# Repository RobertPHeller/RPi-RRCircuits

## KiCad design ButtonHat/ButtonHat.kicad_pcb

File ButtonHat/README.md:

# ButtonHat

This is a RPi HAT board to interface up to 12 push buttons with hardware 
debouncing (using 74ahc14 Hex Schmitt-Trigger Inverters) to a RPi.  Jumpers 
are used to map the buttons to GPIO pins.  This was a simple "thought 
experiment" to see if this was possible.

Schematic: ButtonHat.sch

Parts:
C1, C2, C3, C4, C5, C6, C9, C10, C11, C12, C13, C14: 10 nf; Mouser Part Number 80-C317C103M5U
C7, C8: .1 uf; Mouser Part Number 21RZ310-RC
J0: RPI_GPIO; Mouser Part Number 855-M20-6102045
J1: Buttons 1 to 6; Mouser Part Number 538-90147-1106
J2: Buttons 7 to 12; Mouser Part Number 538-90147-1106
J3: GPIO; Mouser Part Number 517-929974-01-17-RK
R1, R2, R3, R4, R5, R6, R7, R8, R9, R10, R11, R12: 10K Ohms; Mouser Part Number 71-CCF5010K0FKE36
T1: Buttons 1 to 6; Mouser Part Number 651-1725698
T2: Ground; Mouser Part Number 571-282834-2
T3: Buttons 7 to 12; Mouser Part Number 651-1725698
U1, U2: 74AHC14; Mouser Part Number 595-SN74AHC14N

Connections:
+3.3V: C7.1, C8.1, J0.1, J0.17, R1.1, R2.1, R3.1, R4.1, R5.1, R6.1, R7.1, R8.1, R9.1, R10.1, R11.1, R12.1, U1.14 (VCC), U2.14 (VCC)
BCM4, wPi 7: J0.7, J3.8
BCM5, wPi 21: J0.29, J3.9
BCM6, wPi 22: J0.31, J3.10
BCM12, wPi 26: J0.32, J3.14
BCM13, wPi 23: J0.33, J3.11
BCM16, wPi 27: J0.36, J3.15
BCM17, wPi 0: J0.11, J3.1
BCM18, wPi 1: J0.12, J3.2
BCM19, wPi 24: J0.35, J3.12
BCM20, wPi 28: J0.38, J3.16
BCM21, wPi 29: J0.40, J3.17
BCM22, wPi 3: J0.15, J3.4
BCM23, wPi 4: J0.16, J3.5
BCM24, wPi 5: J0.18, J3.6
BCM25, wPi 6: J0.22, J3.7
BCM26, wPi 25: J0.37, J3.13
BCM27, wPi 2: J0.13, J3.3
GND: C1.2, C2.2, C3.2, C4.2, C5.2, C6.2, C7.2, C8.2, C9.2, C10.2, C11.2, C12.2, C13.2, C14.2, J0.6, J0.9, J0.14, J0.20, J0.25, J0.30, J0.34, J0.39, T2.1, T2.2 (PM), U1.7 (GND), U2.7 (GND)
unnamed: J1.3, U1.6
unnamed: J1.2, U1.4
unnamed: J1.1, U1.2
unnamed: J2.5, U2.10
unnamed: J2.4, U2.8
unnamed: J2.3, U2.6
unnamed: J2.2, U2.4
unnamed: J2.1, U2.2
unnamed: J1.6, U1.12
unnamed: J1.5, U1.10
unnamed: J1.4, U1.8
unnamed: J2.6, U2.12
unnamed: C6.1, R6.2, T1.6, U1.13
unnamed: C5.1, R5.2, T1.5, U1.11
unnamed: C4.1, R4.2, T1.4, U1.9
unnamed: C3.1, R3.2, T1.3, U1.5
unnamed: C2.1, R2.2, T1.2, U1.3
unnamed: C1.1, R1.2, T1.1, U1.1
unnamed: C14.1, R12.2, T3.6, U2.13
unnamed: C13.1, R11.2, T3.5, U2.11
unnamed: C12.1, R10.2, T3.4, U2.9
unnamed: C11.1, R9.2, T3.3, U2.5
unnamed: C10.1, R8.2, T3.2, U2.3
unnamed: C9.1, R7.2, T3.1, U2.1

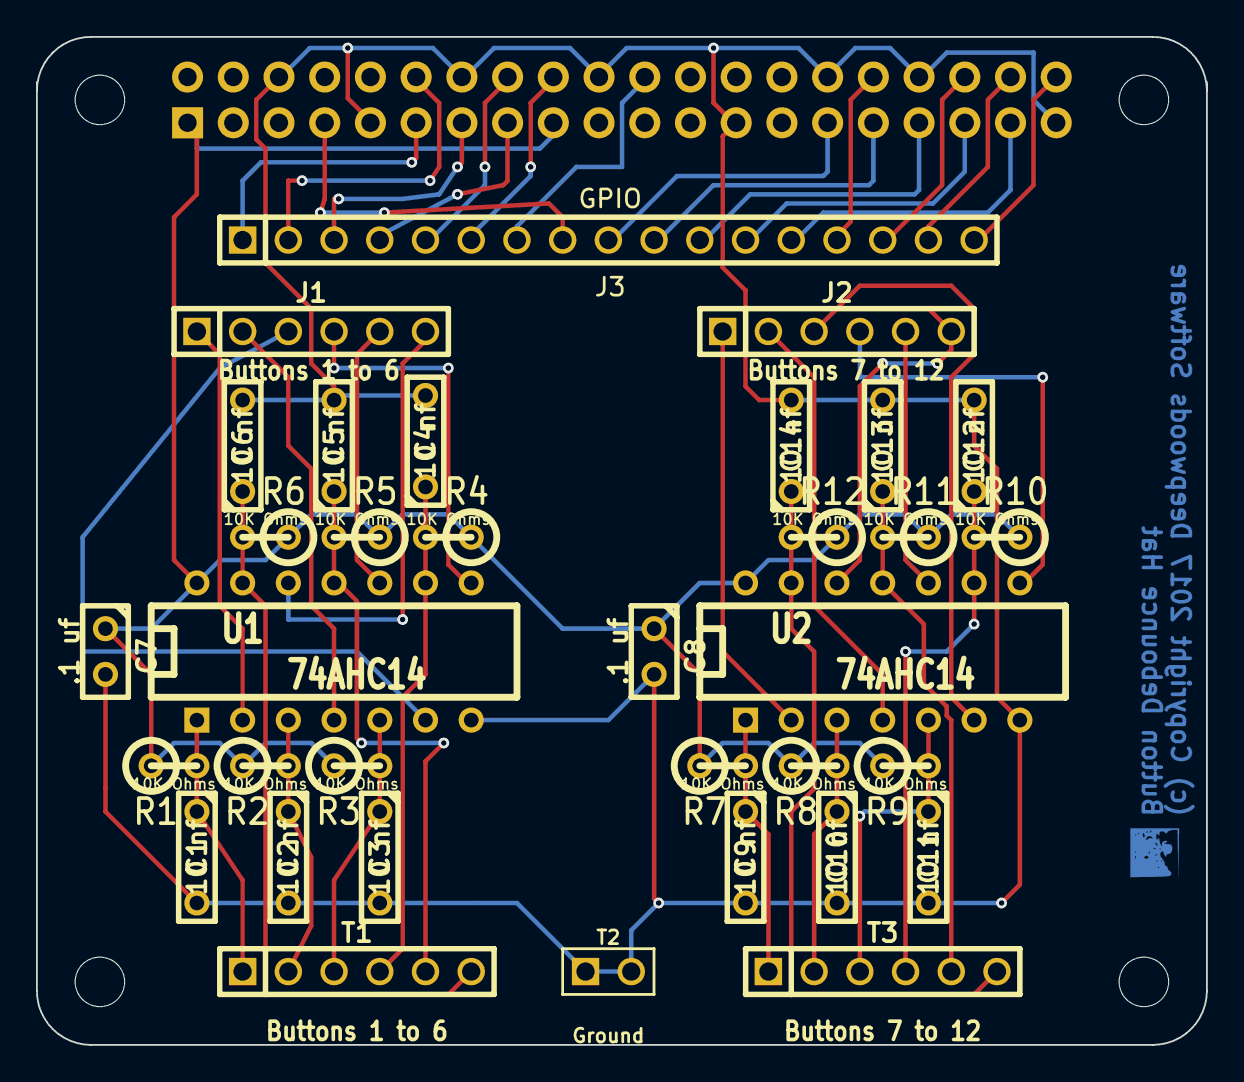
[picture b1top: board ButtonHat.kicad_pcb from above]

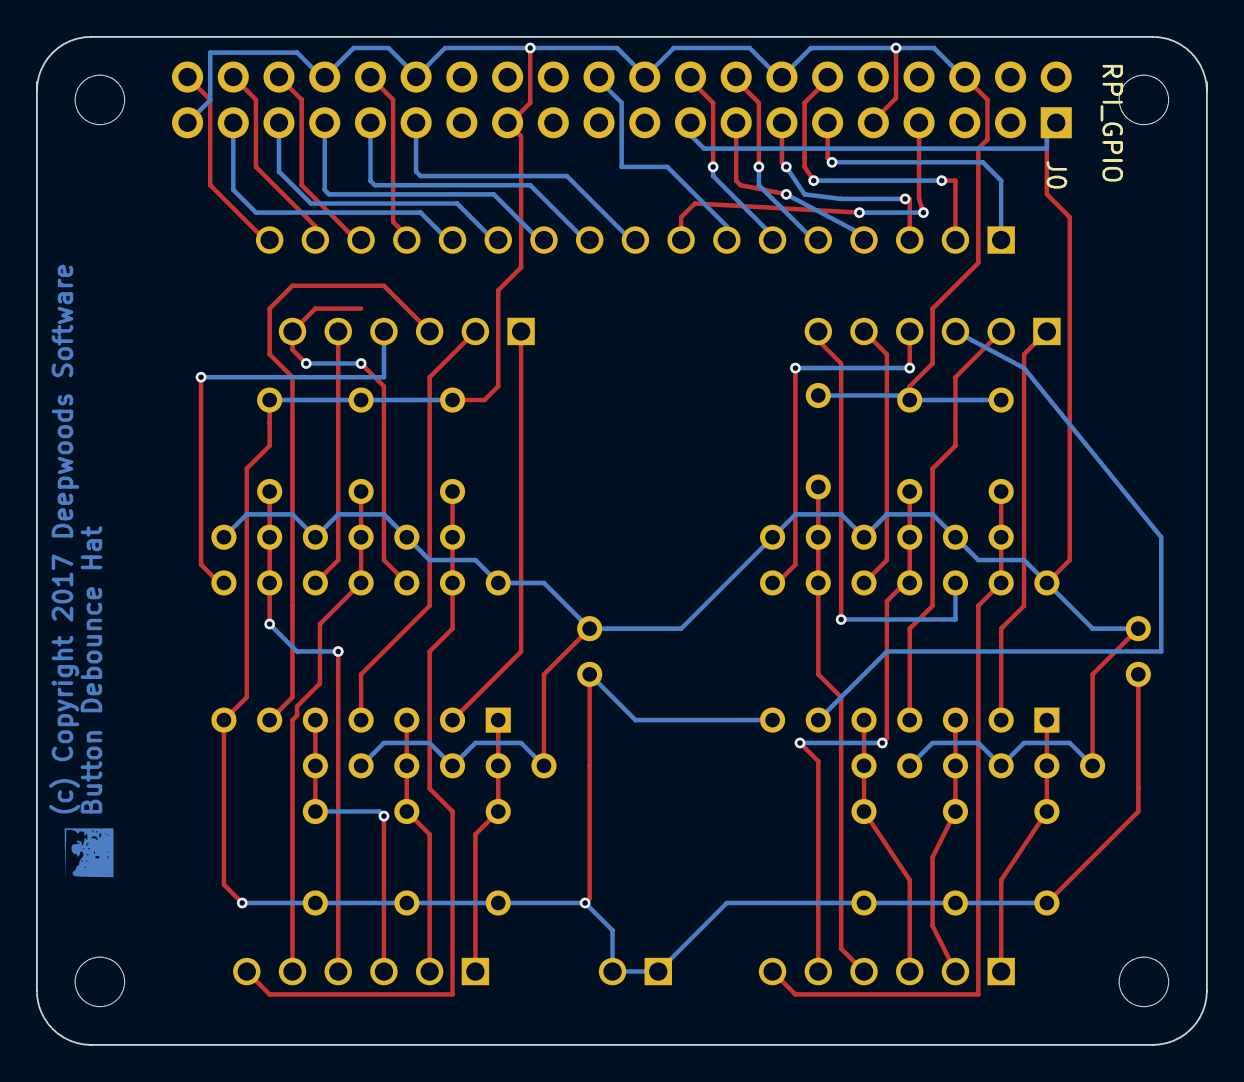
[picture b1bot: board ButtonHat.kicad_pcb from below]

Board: 2 copper layers, 65.0 x 56.0 mm, 39 parts (5 on the bottom side), 43 nets.

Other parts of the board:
H1, H2, H3, H4: RPi_Hat_Mounting_Hole

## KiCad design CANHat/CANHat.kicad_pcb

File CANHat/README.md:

# CANHat

This is the original CAN Hat, using the MCP2515 CAN IF Chip and a MCP2551 
transceiver chip.

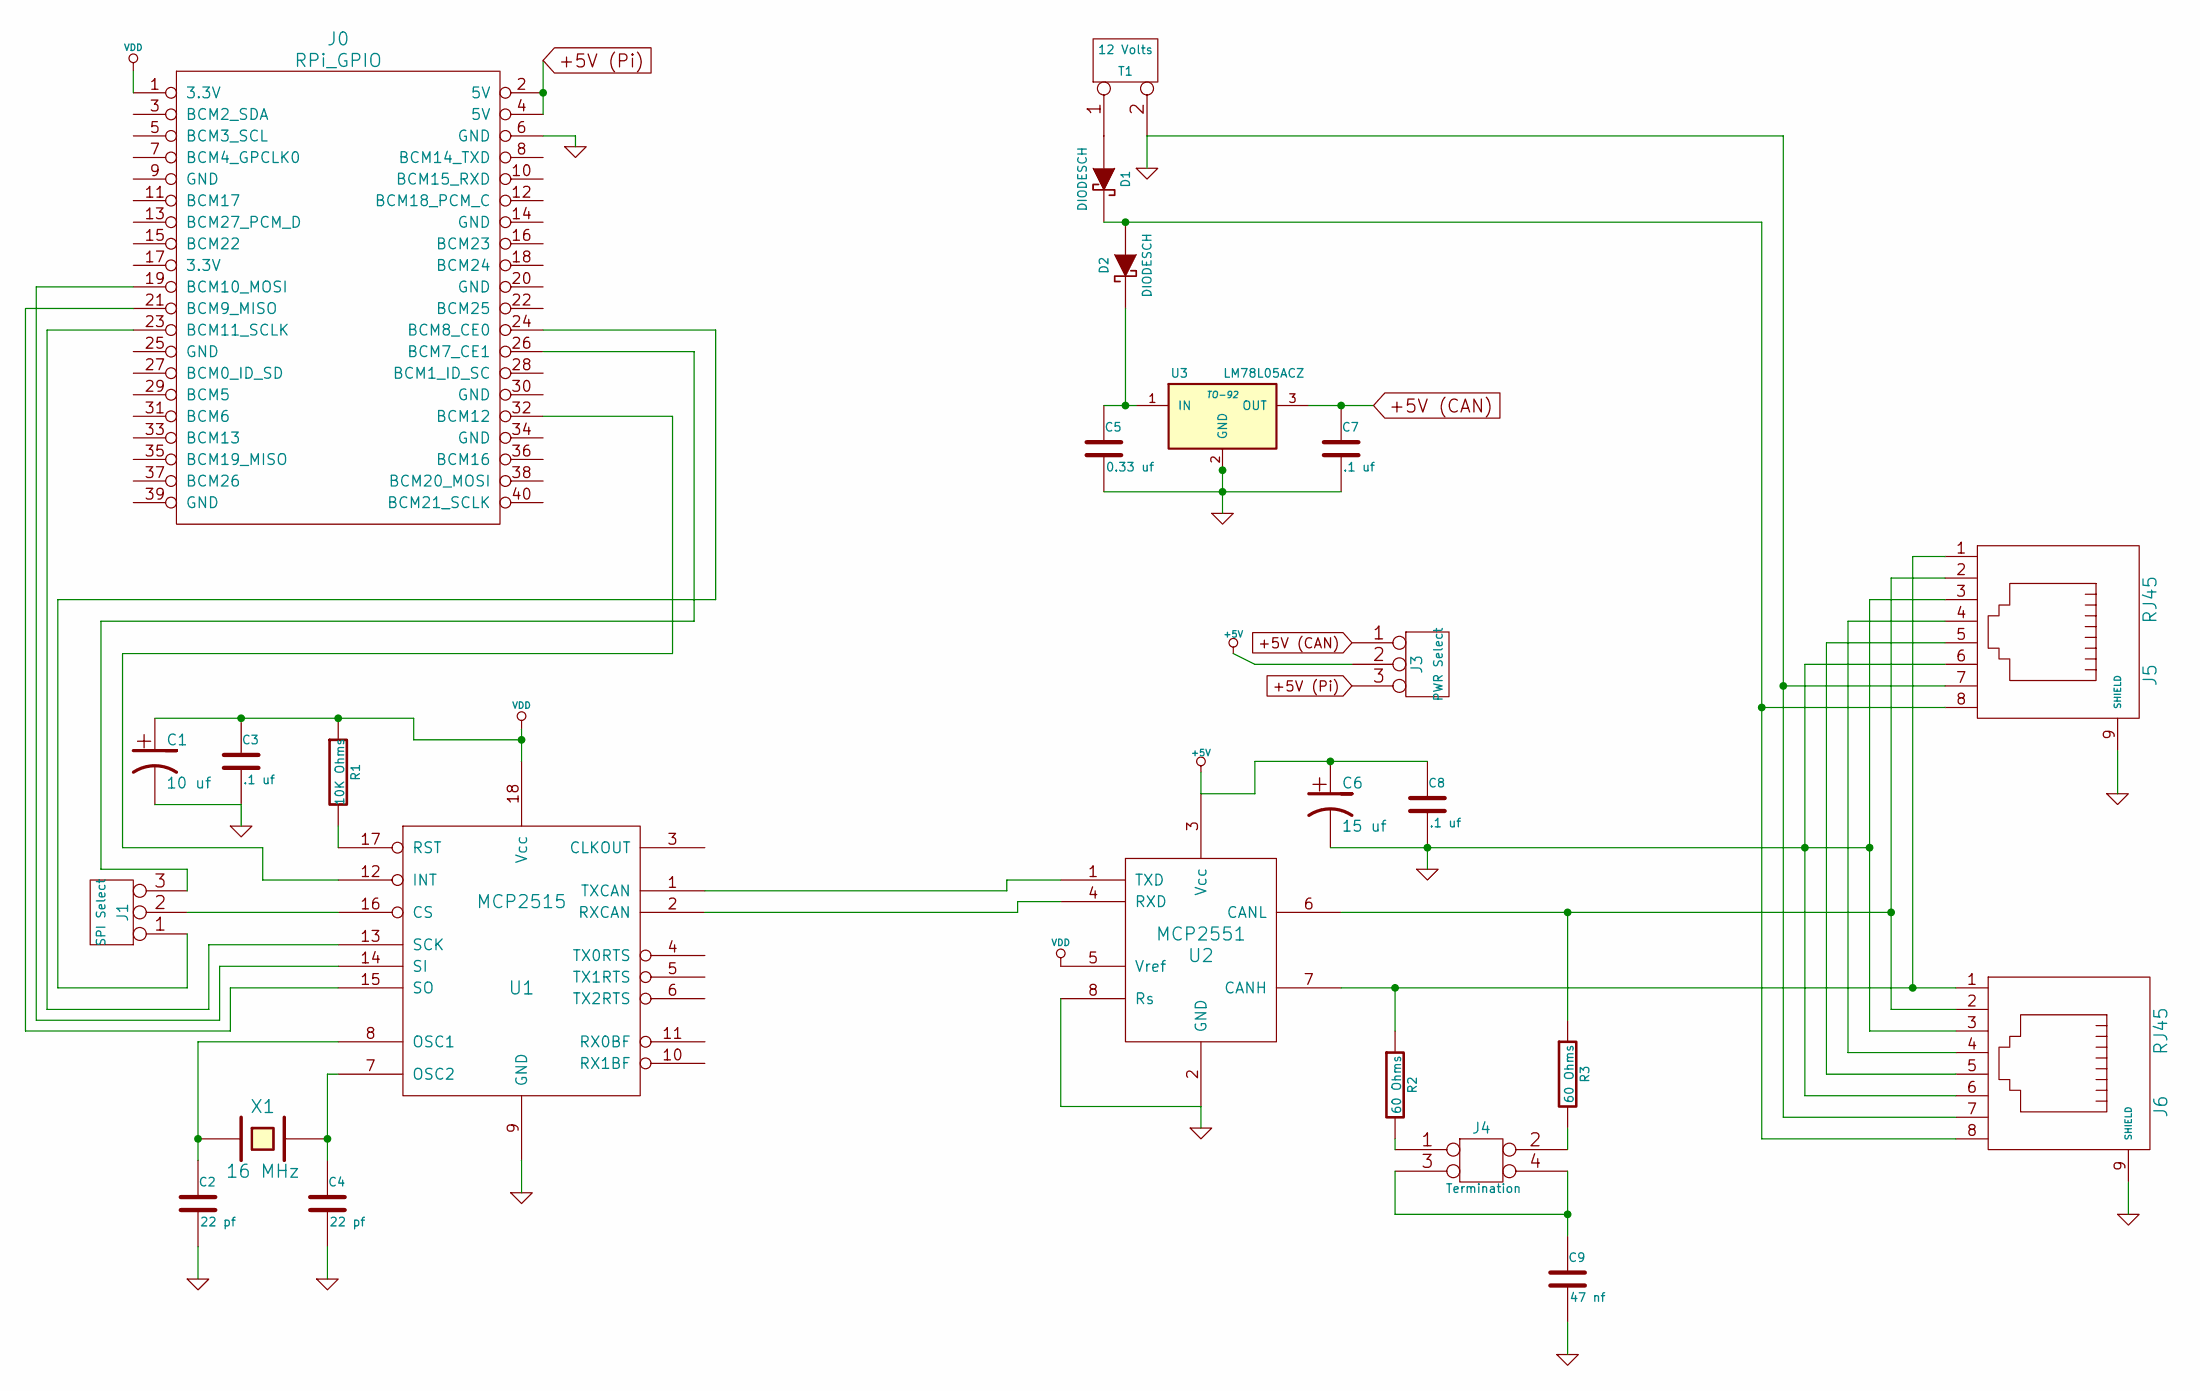
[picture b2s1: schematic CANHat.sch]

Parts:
C1: 10 uf; C1V5; Mouser part Number 667-ECA-1HM100I
C2, C4: 22 pf; C2; Mouser part number 594-K220J10C0GF5UH5
C3: .1 uf; C1; Mouser Part Number 21RZ310-RC
C5: 0.33 uf; Mouser Part Number 75-1C10Z5U334M050B
C6: 15 uf; C1V7; Mouser part number 667-EEA-GA1H150
C7: .1 uf; Mouser Part Number 21RZ310-RC
C8: .1 uf; C1; Mouser Part number 21RZ310-RC
C9: 47 nf; Mouser Part Number 75-1C10Z5U473M050B
D1, D2: DIODESCH; Mouser Part Number 771-BAT86133
J0: RPi_GPIO; Pin_Header_Straight_2x20; Mouser part number 855-M20-6102045
J1: SPI Select; PIN_ARRAY_3X1; Mouser part number 538-22-28-8034
J3: PWR Select; Mouser Part Number 538-22-28-8034
J4: Termination; Mouser Part Number 649-67997-404HLF
J5, J6: RJ45; RJ45-8N-S; Mouser part number 592-RJ45-8N-S
R1: 10K Ohms; R1; Mouser part number 603-CFR-25JR-5210K
R2, R3: 60 Ohms; Mouser Part Number 71-RN60C60R0B/R
T1: 12 Volts; Mouser Part Number 571-1776118-2
U1: MCP2515; DIP-18_300; Mouser part number 579-MCP2515-I/P
U2: MCP2551; DIP-8_300; Mouser part number 579-MCP2551-I/P
U3: LM78L05ACZ; TO-92; Mouser Part Number 512-LM78L05ACZ
X1: 16 MHz; HC-49V; Mouser part number 449-LFXTAL027945BULK

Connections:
+5V: C6.1, C8.1, J3.2 (PM), U2.3 (Vcc)
+5V (CAN): C7.1, J3.1, U3.3 (OUT)
+5V (Pi): J0.2 (5V), J0.4 (5V), J3.3
GND: C1.2, C2.2, C3.2, C4.2, C5.2, C6.2, C7.2, C8.2, C9.2, J0.6 (GND), J5.3, J5.6, J5.7, J5.9 (SHIELD), J6.3, J6.6, J6.7, J6.9 (SHIELD), T1.2 (PM), U1.9 (GND), U2.2 (GND), U2.8 (Rs), U3.2 (GND)
unnamed: J0.21 (BCM9_MISO), U1.15 (SO)
unnamed: D1.2 (K), D2.1 (A), J5.8, J6.8
unnamed: J5.5, J6.5
unnamed: J5.4, J6.4
unnamed: J0.32 (BCM12), U1.12 (INT)
unnamed: J0.19 (BCM10_MOSI), U1.14 (SI)
unnamed: J0.23 (BCM11_SCLK), U1.13 (SCK)
unnamed: J0.24 (BCM8_CE0), J1.1
unnamed: J0.26 (BCM7_CE1), J1.3
unnamed: J4.1, R2.2
unnamed: J4.2, R3.2
unnamed: J5.1, J6.1, R2.1, U2.7 (CANH)
unnamed: J5.2, J6.2, R3.1, U2.6 (CANL)
unnamed: C9.1, J4.3, J4.4
unnamed: D1.1 (A), T1.1
unnamed: C5.1, D2.2 (K), U3.1 (IN)
unnamed: J1.2 (PM), U1.16 (CS)
unnamed: U1.2 (RXCAN), U2.4 (RXD)
unnamed: U1.1 (TXCAN), U2.1 (TXD)
unnamed: R1.2, U1.17 (RST)
unnamed: C4.1, U1.7 (OSC2), X1.2
unnamed: C2.1, U1.8 (OSC1), X1.1
VDD: C1.1, C3.1, J0.1 (3.3V), R1.1, U1.18 (Vcc), U2.5 (Vref)

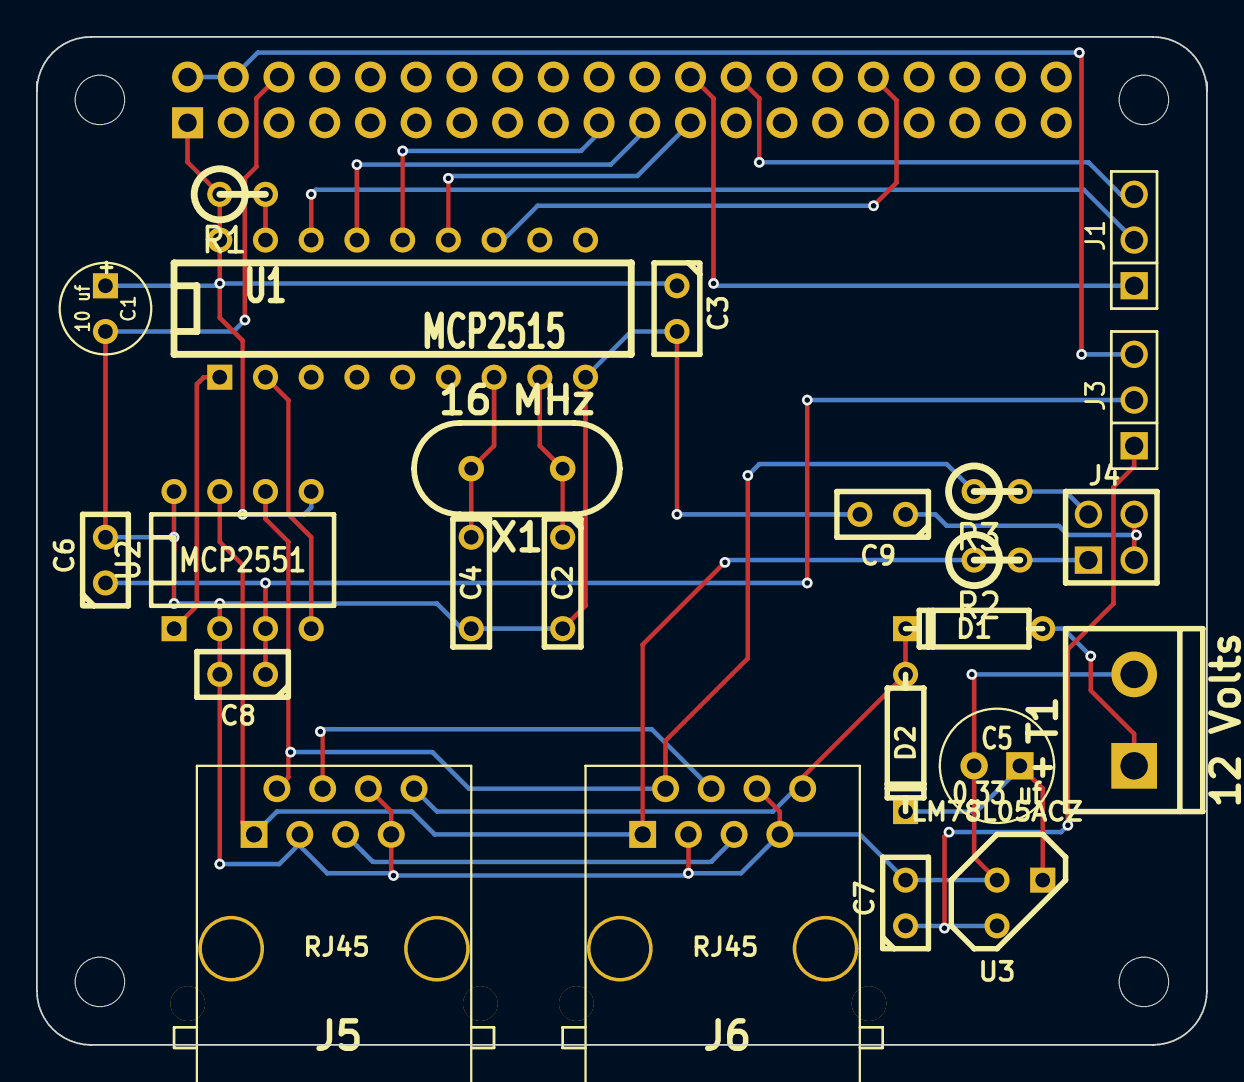
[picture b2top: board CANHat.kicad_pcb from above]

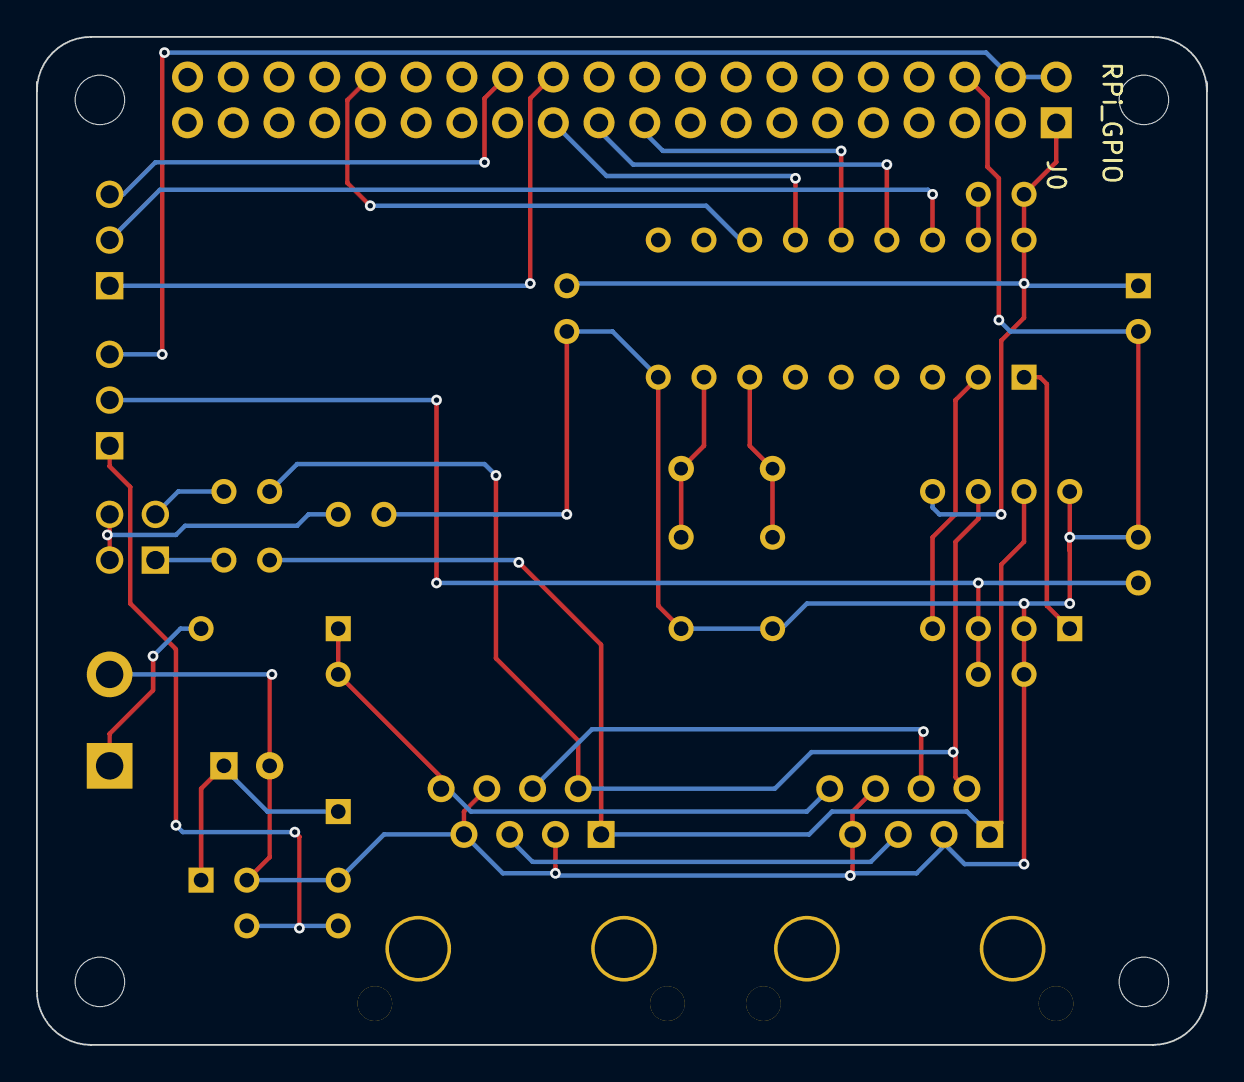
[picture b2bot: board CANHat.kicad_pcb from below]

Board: 2 copper layers, 65.0 x 56.0 mm, 29 parts (5 on the bottom side), 27 nets.

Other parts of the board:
H1, H2, H3, H4: RPi_Hat_Mounting_Hole

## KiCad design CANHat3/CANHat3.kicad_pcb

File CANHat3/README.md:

# CANHat3

This is the third incarnation of the CAN Hat, also using the MCP2515 and 
MCP2551 chips.

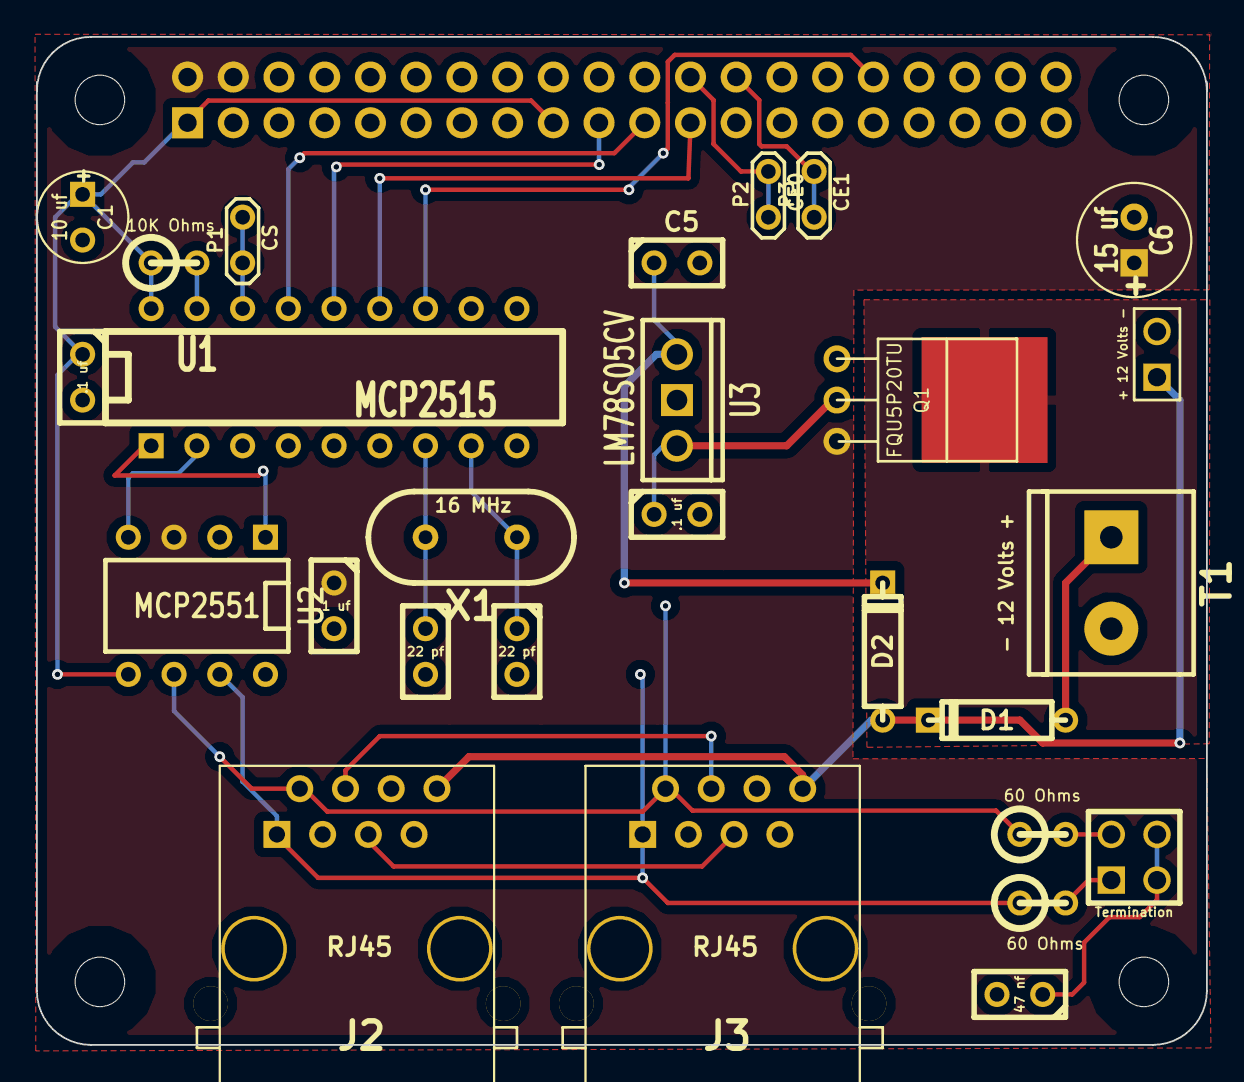
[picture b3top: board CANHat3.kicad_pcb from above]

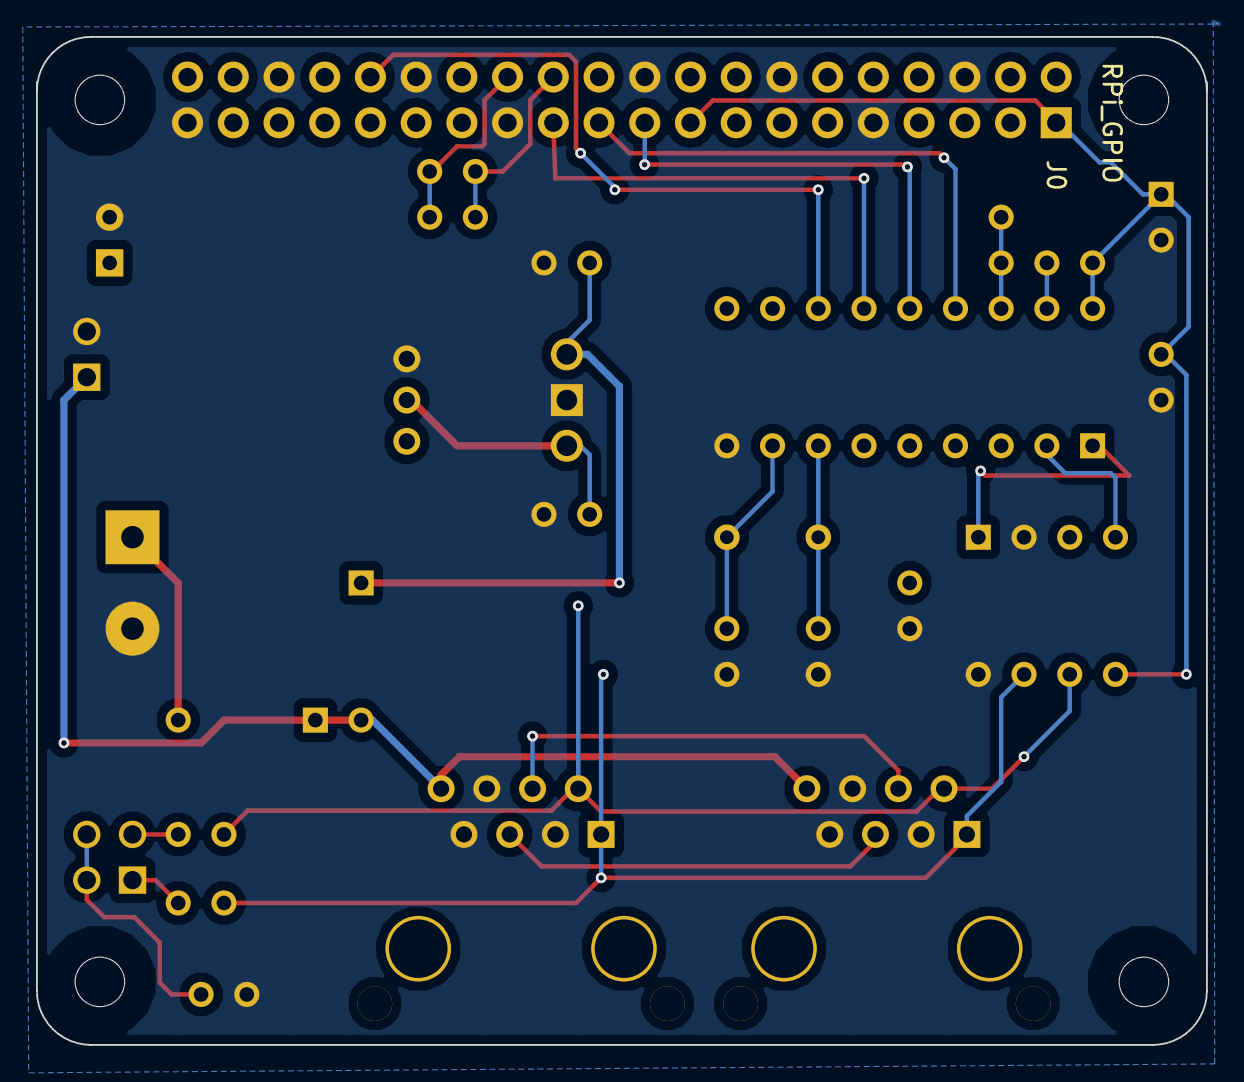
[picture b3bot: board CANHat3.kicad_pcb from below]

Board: 2 copper layers, 65.0 x 56.0 mm, 32 parts (5 on the bottom side), 26 nets.

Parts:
C1: 10 uf; C1V5
C2, C4: 22 pf; C1
C3, C7, C8: .1 uf; C1
C5: 0.33 uf; C1
C6: 15 uf; C1V7
C9: 47 nf; C1
D1, D2: SB240-E3/54; D3
H1, H2, H3, H4: RPi_Hat_Mounting_Hole
J0: RPi_GPIO; Pin_Header_Straight_2x20
J1: Termination; PIN_ARRAY_2X2
J2, J3: RJ45; RJ45_8N-S
P1: CS; TESTPOINT
P2: CE0; TESTPOINT
P3: CE1; TESTPOINT
P4: + 12 Volts -; ScrewTerm2.54-2
Q1: FQU5P20TU; TO-251-3
R1: 10K Ohms; R1
R2, R3: 60 Ohms; R1
T1: - 12 Volts +; mors_2p
U1: MCP2515; DIP-18__300
U2: MCP2551; DIP-8__300
U3: LM78S05CV; LM78XXV
X1: 16 MHz; HC-49V

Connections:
+3.3V: C1.1, C3.1, J0.1, J0.17, R1.1, U1.18, U2.5
+5V: C6.1, C8.1, J0.2, J0.4, Q1.S, U2.3
+12V: D1.2, D2.1, J2.8, J3.8, P4.1
CS: P1.1, U1.16
GND: C1.2, C2.2, C3.2, C4.2, C5.2, C6.2, C7.2, C8.2, C9.2, J0.6, J0.9, J0.14, J0.20, J0.25, J0.30, J0.36, J0.39, J2.3, J2.6, J2.7, J3.3, J3.6, J3.7, P4.2, Q1.G, T1.2, U1.9, U2.2, U2.8, U3.GND
INT: J0.32, U1.12
MISO: J0.21, U1.15
MOSI: J0.19, U1.14
unnamed: J1.1, R2.2
unnamed: J1.2, R3.2
unnamed: C9.1, J1.3, J1.4
unnamed: C5.1, D2.2, U3.VI
unnamed: D1.1, T1.1
unnamed: C7.1, Q1.D, U3.VO
unnamed: J0.26, P3.1
unnamed: J0.24, P2.1
unnamed: U1.1, U2.1
unnamed: R1.2, U1.17
unnamed: J2.4, J3.4
unnamed: J2.2, J3.2, R3.1, U2.6
unnamed: J2.5, J3.5
unnamed: U1.2, U2.4
unnamed: C4.1, U1.7, X1.2
unnamed: C2.1, U1.8, X1.1
unnamed: J2.1, J3.1, R2.1, U2.7
SCLK: J0.23, U1.13

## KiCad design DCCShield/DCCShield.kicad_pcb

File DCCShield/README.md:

# DCCShield

Simple DCC driver shield for Arduino.

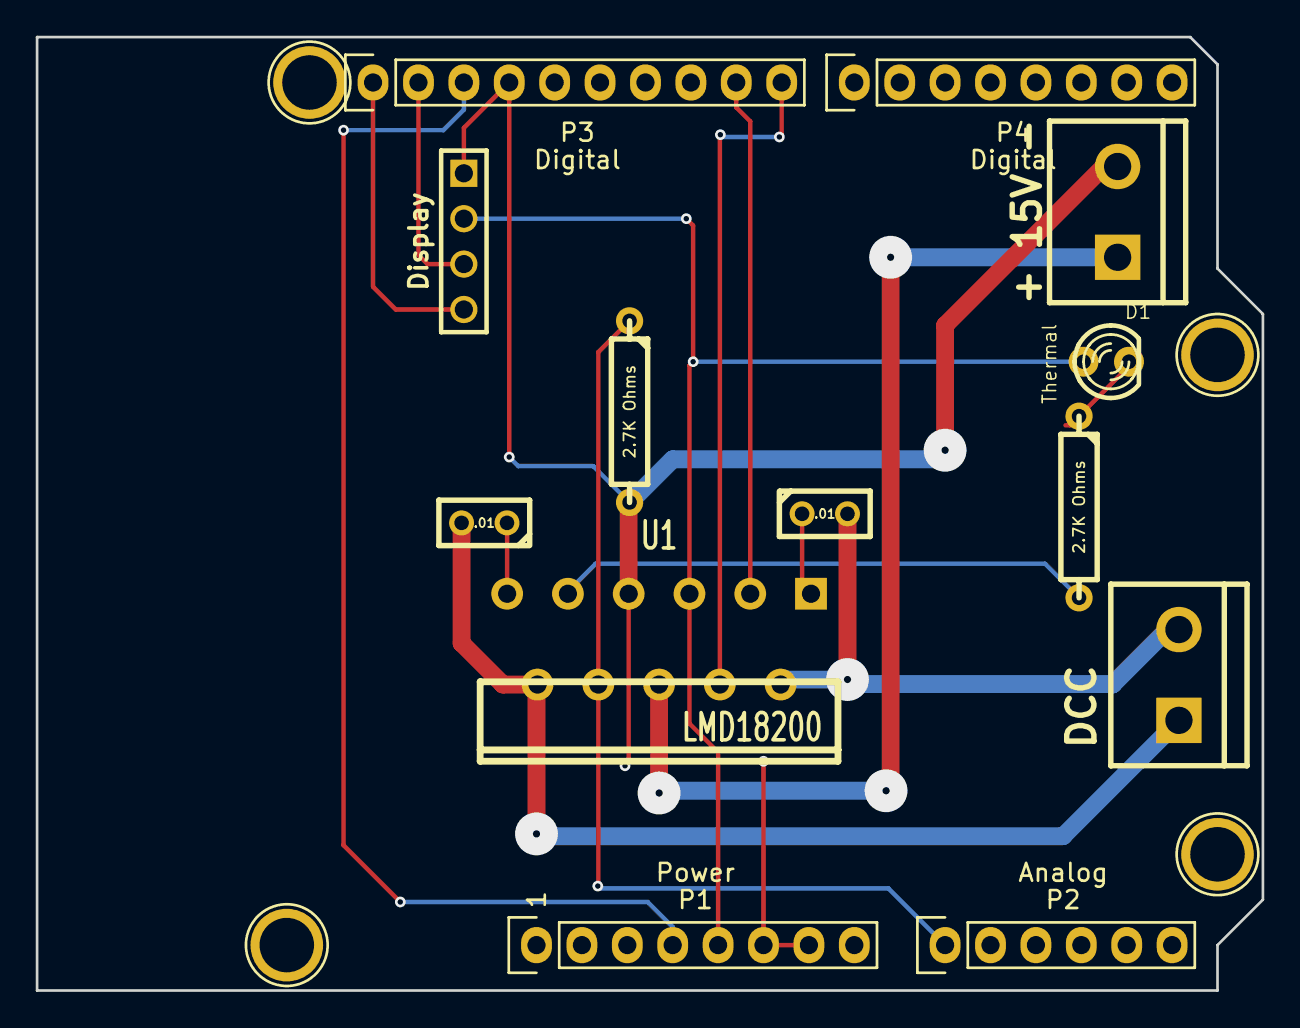
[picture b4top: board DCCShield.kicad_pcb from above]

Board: 2 copper layers, 68.6 x 53.3 mm, 17 parts (0 on the bottom side), 15 nets.

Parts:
C1, C2: .01; C1
D1: Thermal; LED-3MM
P1: Power; Socket_Strip_Arduino_1x08
P2: Analog; Socket_Strip_Arduino_1x06
P3: Digital; Socket_Strip_Arduino_1x10
P4: Digital; Socket_Strip_Arduino_1x08
P5, P6, P7, P8: CONN_01X01; Arduino_1pin
P9: + 15V -; bornier2
P10: DCC; bornier2
P11: Display; PIN_ARRAY_4x1
R1, R2: 2.7K Ohms; R4
U1: LMD18200; TO220_11PIN_VERT

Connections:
+3.3V: P1.4, P3.3
+5V: D1.1, P1.5, P11.2, U1.5
/8: P3.10, U1.4
/9: P3.9, U1.3
/+15V (TRK Power): P9.1, U1.6
/A0: P2.1, R1.1, U1.8
/A4(SDA): P2.5, P3.2, P11.3
/A5(SCL): P2.6, P3.1, P11.4
/DCC Out 1: C2.2, P10.1, U1.10
/DCC Out 2: C1.2, P10.2, U1.2
GND: P1.6, P1.7, P3.4, P9.2, P11.1, R1.2, U1.7
unnamed: C1.1, U1.1
unnamed: C2.1, U1.11
unnamed: D1.2, R2.1
unnamed: R2.2, U1.9

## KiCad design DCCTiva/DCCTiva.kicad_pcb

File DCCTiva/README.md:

# DCCTiva

Simple DCC Driver board for Tiva.

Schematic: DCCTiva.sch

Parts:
C1, C2: .01 uf
D1: Thermal Warning
J1: TI_BOOSTER_40_J1
J2: TI_BOOSTER_40_J2
J3: TI_BOOSTER_40_J3
J4: TI_BOOSTER_40_J4
J5: CONN_3
P1: Power and DCC
P2: I2C 1
P3: I2C 0
R1, R2: 2.7K Ohms
U1: LMD18200

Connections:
+5V: D1.1 (A), J3.1, P2.2, P3.2
/+15V: P1.1, U1.6 (Vcc)
/Current Sense: J3.9, R1.1, U1.8 (CurSense)
/DCC A: C1.2, P1.3, U1.2 (Out_1)
/DCC B: C2.2, P1.4, U1.10 (Out_2)
/Enable: J4.5, U1.4 (Brake)
/PWM: J4.1, U1.3 (Dir)
/SCL - 0: J2.2, P3.4
/SCL - 1: J1.9, P2.4
/SDA - 0: J4.3, P3.3
/SDA - 1: J1.10, P2.3
GND: J2.1, J3.2, J5.2 (PM), J5.3, P1.2, P2.1, P3.1, R1.2, U1.7 (GND)
unnamed: R2.2, U1.9 (Thermal)
unnamed: D1.2 (K), R2.1
unnamed: C1.1, U1.1 (Boot_1)
unnamed: C2.1, U1.11 (Boot_2)
VCC: J1.1, J5.1, U1.5 (PWM)

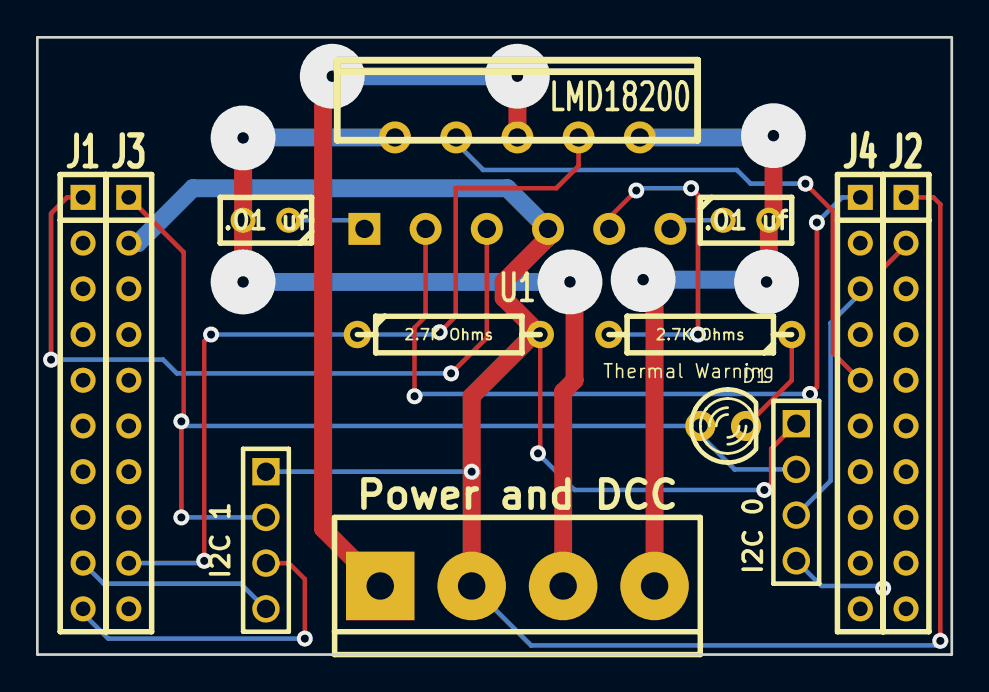
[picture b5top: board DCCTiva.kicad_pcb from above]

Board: 2 copper layers, 50.8 x 34.3 mm, 13 parts (0 on the bottom side), 17 nets.

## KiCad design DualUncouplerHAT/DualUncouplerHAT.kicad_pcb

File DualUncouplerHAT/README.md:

# DualUncouplerHAT

This a dual driver for a electromagnetic uncoupler coil.  It features a 
pair of 555 type timers (in the form of a 556 dual timer) driving a TIP120 
power darlington.  It uses GPIO pins 21 and 22 (BCM 5 and 6, physical pins 
29 and 31).

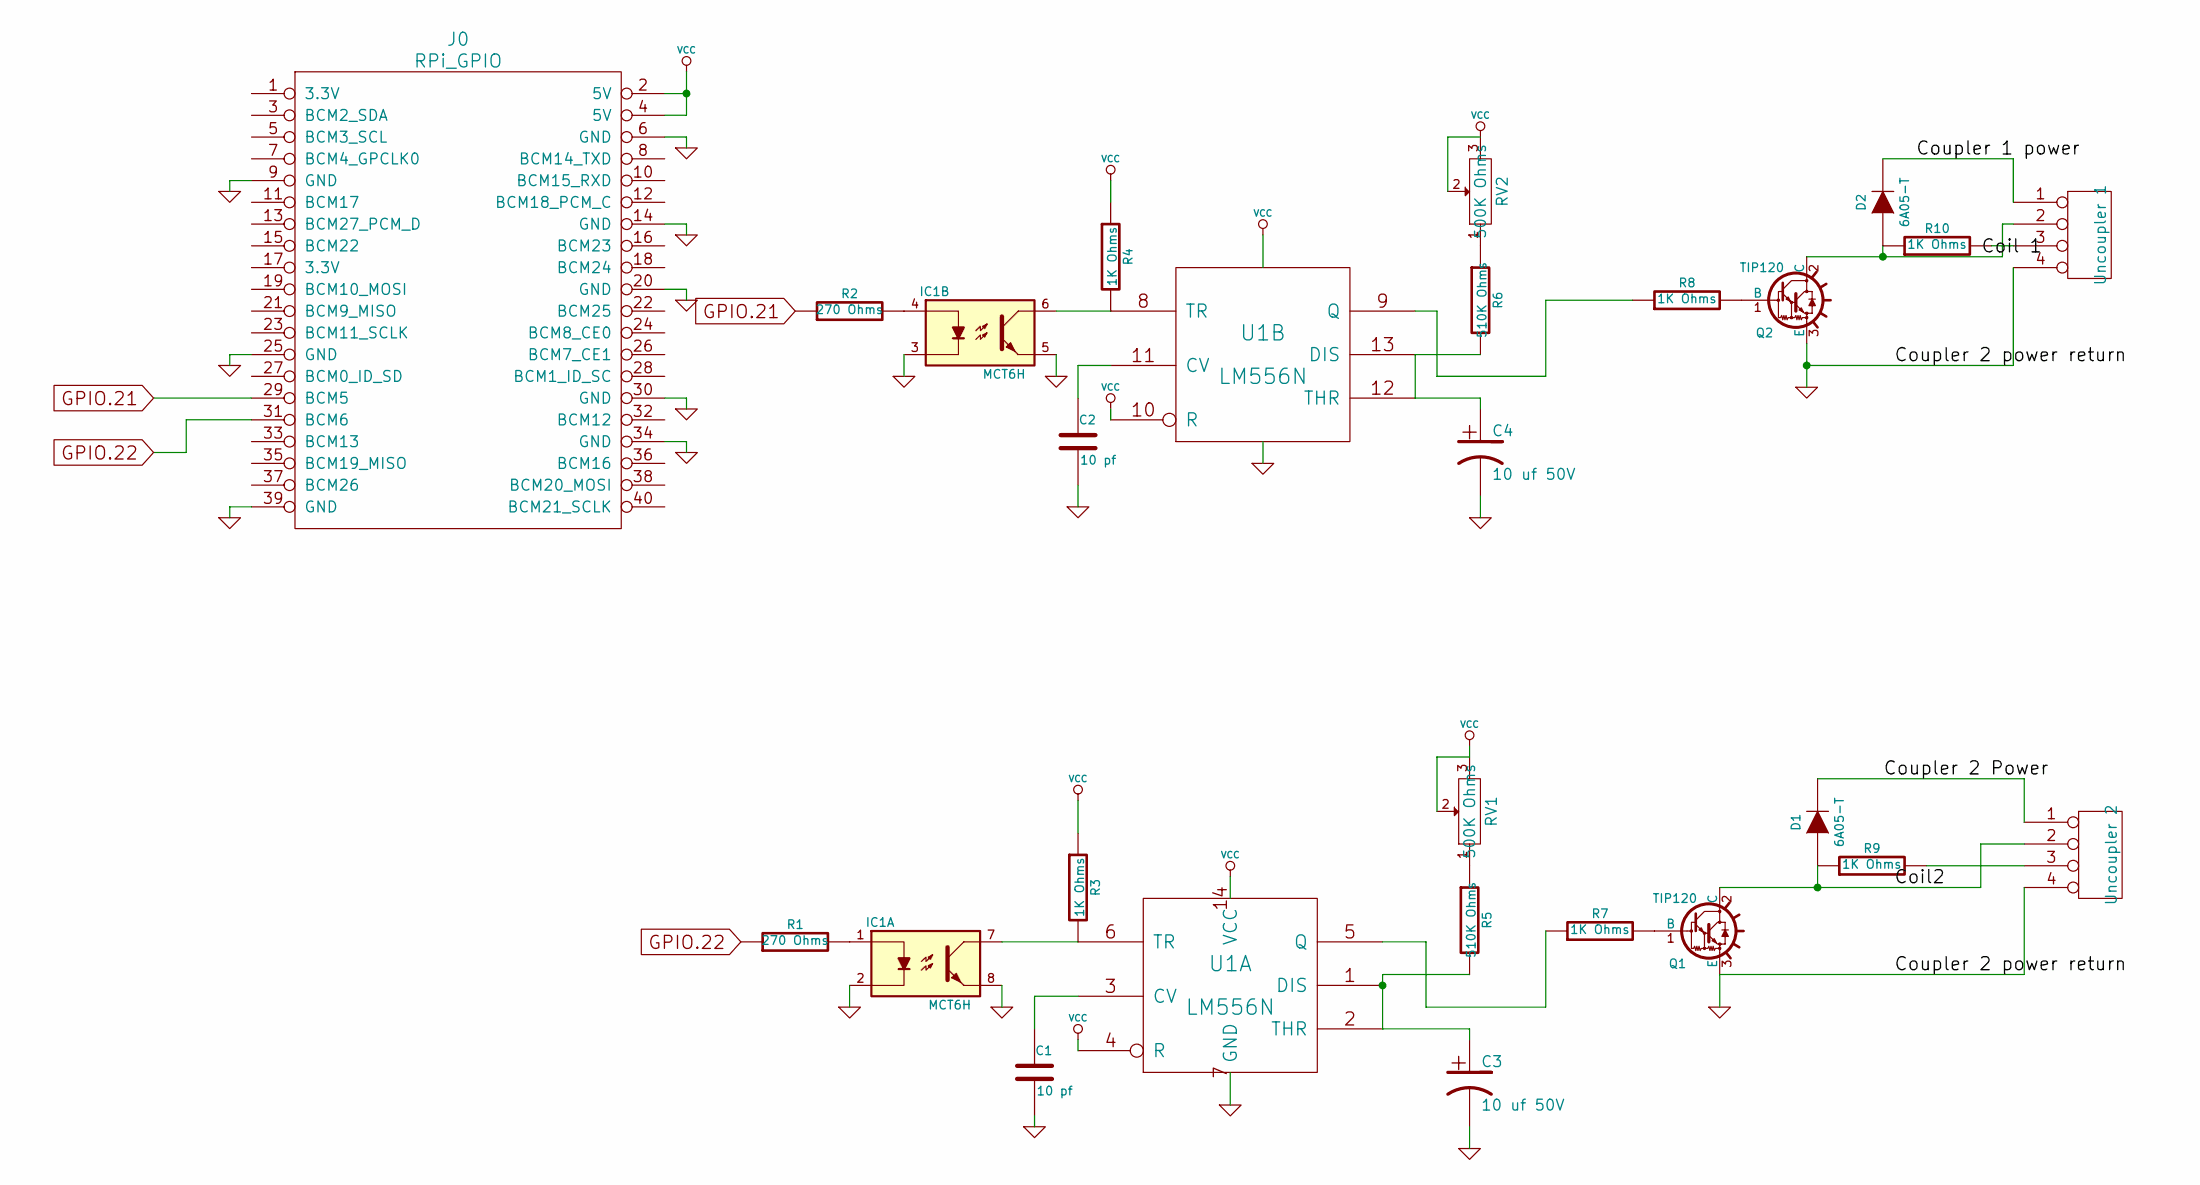
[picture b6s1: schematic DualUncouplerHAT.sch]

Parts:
C1, C2: 10 pf; Mouser Part Number 594-S100K25SL0N63L6R
C3, C4: 10 uf 50V; Mouser Part Number 140-REA100M1HBK0511P
D1, D2: 6A05-T; Mouser Part Number 621-6A05-T
IC1: MCT6H; DIP-8__300; Mouser Part Number 782-MCT6H
J0: RPi_GPIO; Pin_Header_Straight_2x20; Mouser Part Number 855-M20-6102045
Q1, Q2: TIP120; TO220; Mouser Part Number 863-TIP120G
R1, R2: 270 Ohms; Mouser Part Number 603-CFR-25JR-52-270R
R3, R4, R7, R8, R9, R10: 1K Ohms; Mouser Part Number 279-2-1623927-3
R5, R6: 510K Ohms; Mouser Part Number 660-CF1/4CT52R514J
RV1, RV2: 500K Ohms; Mouser Part Number 652-3309P-1-504
T1: Uncoupler 1; Mouser Part Number 571-2828374
T2: Uncoupler 2; Mouser Part Number 571-2828374
U1: LM556N

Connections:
/Coil2: D1.1 (A), Q1.2 (C), R9.1, T2.2
/Coil 1: D2.1 (A), Q2.2 (C), R10.1, T1.2
/Coupler 1 power: D2.2 (K), T1.1
/Coupler 2 Power: D1.2 (K), T2.1
GND: C1.2, C2.2, C3.2, C4.2, IC1.2, IC1.3, IC1.5, IC1.8, J0.6 (GND), J0.9 (GND), J0.14 (GND), J0.20 (GND), J0.25 (GND), J0.30 (GND), J0.34 (GND), J0.39 (GND), Q1.3 (E), Q2.3 (E), T1.4, T2.4, U1.7 (GND)
GPIO.21: J0.29 (BCM5), R2.1
GPIO.22: J0.31 (BCM6), R1.1
unnamed: C1.1, U1.3 (CV)
unnamed: C2.1, U1.11 (CV)
unnamed: IC1.7, R3.2, U1.6 (TR)
unnamed: IC1.6, R4.2, U1.8 (TR)
unnamed: R9.2, T2.3
unnamed: R10.2, T1.3
unnamed: R7.1, U1.5 (Q)
unnamed: C4.1, R6.2, U1.12 (THR), U1.13 (DIS)
unnamed: R8.1, U1.9 (Q)
unnamed: C3.1, R5.2, U1.1 (DIS), U1.2 (THR)
unnamed: Q2.1 (B), R8.2
unnamed: R5.1, RV1.1
unnamed: R6.1, RV2.1
unnamed: Q1.1 (B), R7.2
unnamed: IC1.1, R1.2
unnamed: IC1.4, R2.2
VCC: J0.2 (5V), J0.4 (5V), R3.1, R4.1, RV1.2, RV1.3, RV2.2, RV2.3, U1.4 (R), U1.10 (R), U1.14 (VCC)

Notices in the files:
ButtonHat/ButtonHat.kicad_pcb:
(c) Copyright 2017 Deepwoods Software
DualUncouplerHAT/DualUncouplerHAT.kicad_pcb:
Copyright 2016 Deepwoods Software
